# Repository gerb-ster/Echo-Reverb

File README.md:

# Echo/Reverb

Next, another effect module. I bought a bunch of PT2399 IC’s from China so I made his Echo/Reverb unit. It’s basically a clone of the Echo unit from Synthrotek.

## Status: Finished

- done: first schematic & board design
- done: breadboard and test
- done: design frontpanel
- done: order PCB and build prototype

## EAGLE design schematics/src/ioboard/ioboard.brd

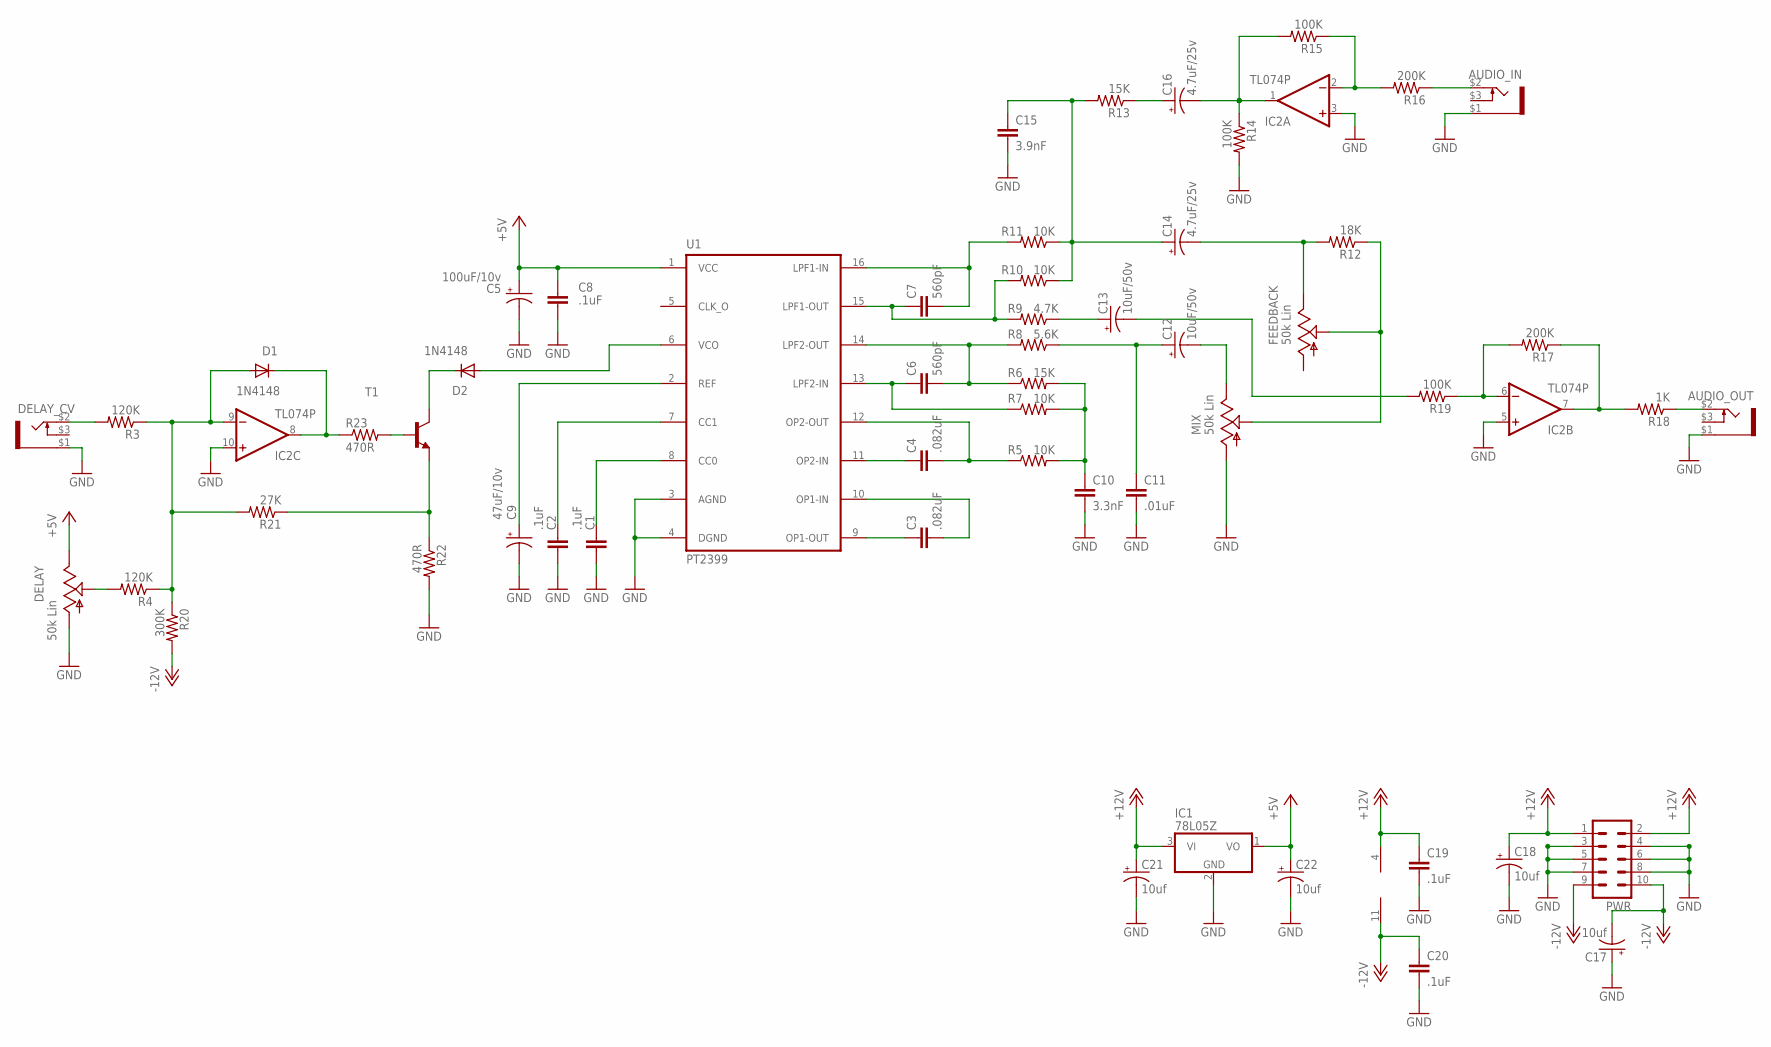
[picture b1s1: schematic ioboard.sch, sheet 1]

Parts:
AUDIO_IN: PJ-323PJ-323; PJ-323
AUDIO_OUT: PJ-323PJ-323; PJ-323
C1, C2, C8, C19, C20: .1uF; C050-024X044
C3, C4: .082uF; C050-024X044
C5: 100uF/10v; E2,5-6
C6, C7: 560pF; C050-024X044
C9: 47uF/10v; E2,5-6
C10: 3.3nF; C050-024X044
C11: .01uF; C050-024X044
C12, C13: 10uF/50v; E2,5-6
C14, C16: 4.7uF/25v; E2,5-6
C15: 3.9nF; C050-024X044
C17, C18, C21, C22: 10uf; E2,5-5
D1, D2: 1N4148; DO35-7
DELAY: 50k Lin; EVUF
DELAY_CV: PJ-323PJ-323; PJ-323
FEEDBACK: 50k Lin; EVUF
IC1: 78L05Z; TO92
IC2: TL074P; DIL14
MIX: 50k Lin; EVUF
PWR: ML10
R3, R4: 120K; 0207/7
R5, R7, R10, R11: 10K; 0207/7
R6, R13: 15K; 0207/7
R8: 5.6K; 0207/7
R9: 4.7K; 0207/7
R12: 18K; 0207/7
R14, R15, R19: 100K; 0207/7
R16, R17: 200K; 0207/7
R18: 1K; 0207/7
R20: 300K; 0207/7
R21: 27K; 0207/7
R22, R23: 470R; 0207/7
T1: 2N3904-NPN-TO92-EBC; TO92-EBC
U1: PT2399; DIL16

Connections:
+5V: C5.+, C8.1, C22.+, DELAY.3 (E), IC1.1 (VO), U1.1 (VCC)
+12V: C18.+, C19.1, C21.+, IC1.3 (VI), IC2.4 (V+), PWR.1, PWR.2
-12V: C17.-, C20.1, IC2.11 (V-), PWR.9, PWR.10, R20.2
DELAY: D2.A, U1.6 (VCO)
GND: AUDIO_IN.$1 (3), AUDIO_OUT.$1 (3), C1.2, C2.2, C5.-, C8.2, C9.-, C10.2, C11.2, C15.2, C17.+, C18.-, C19.2, C20.2, C21.-, C22.-, DELAY.1 (A), DELAY_CV.$1 (3), IC1.2 (GND), IC2.3 (+IN), IC2.5 (+IN), IC2.10 (+IN), MIX.1 (A), PWR.3, PWR.4, PWR.5, PWR.6, PWR.7, PWR.8, R14.2, R22.2, U1.3 (AGND), U1.4 (DGND)
unnamed: C1.1, U1.8 (CC0)
unnamed: C2.1, U1.7 (CC1)
unnamed: C3.2, U1.10 (OP1-IN)
unnamed: C3.1, U1.9 (OP1-OUT)
unnamed: C4.1, U1.11 (OP2-IN)
unnamed: C4.2, R5.1, U1.12 (OP2-OUT)
unnamed: C6.1, R7.1, U1.13 (LPF2-IN)
unnamed: C7.1, R9.2, R10.2, U1.15 (LPF1-OUT)
unnamed: C6.2, R6.1, R8.2, U1.14 (LPF2-OUT)
unnamed: C7.2, R11.2, U1.16 (LPF1-IN)
unnamed: C9.+, U1.2 (REF)
unnamed: C10.1, R5.2, R6.2, R7.2
unnamed: C11.1, C12.+, R8.1
unnamed: C12.-, MIX.3 (E)
unnamed: C13.+, R9.1
unnamed: C14.+, C15.1, R10.1, R11.1, R13.2
unnamed: C14.-, FEEDBACK.3 (E), R12.2
unnamed: FEEDBACK.2 (S), MIX.2 (S), R12.1
unnamed: C16.+, R13.1
unnamed: C16.-, IC2.1 (OUT), R14.1, R15.2
unnamed: IC2.6 (-IN), R17.2, R19.1
unnamed: AUDIO_IN.$2 (1), R16.1
unnamed: IC2.2 (-IN), R15.1, R16.2
unnamed: IC2.7 (OUT), R17.1, R18.2
unnamed: AUDIO_OUT.$2 (1), R18.1
unnamed: DELAY.2 (S), R4.2
unnamed: DELAY_CV.$2 (1), R3.2
unnamed: D1.A, IC2.9 (-IN), R3.1, R4.1, R20.1, R21.2
unnamed: D1.C, IC2.8 (OUT), R23.1
unnamed: R21.1, R22.1, T1.E
unnamed: R23.2, T1.B
unnamed: D2.C, T1.C
OUT: C13.-, R19.2

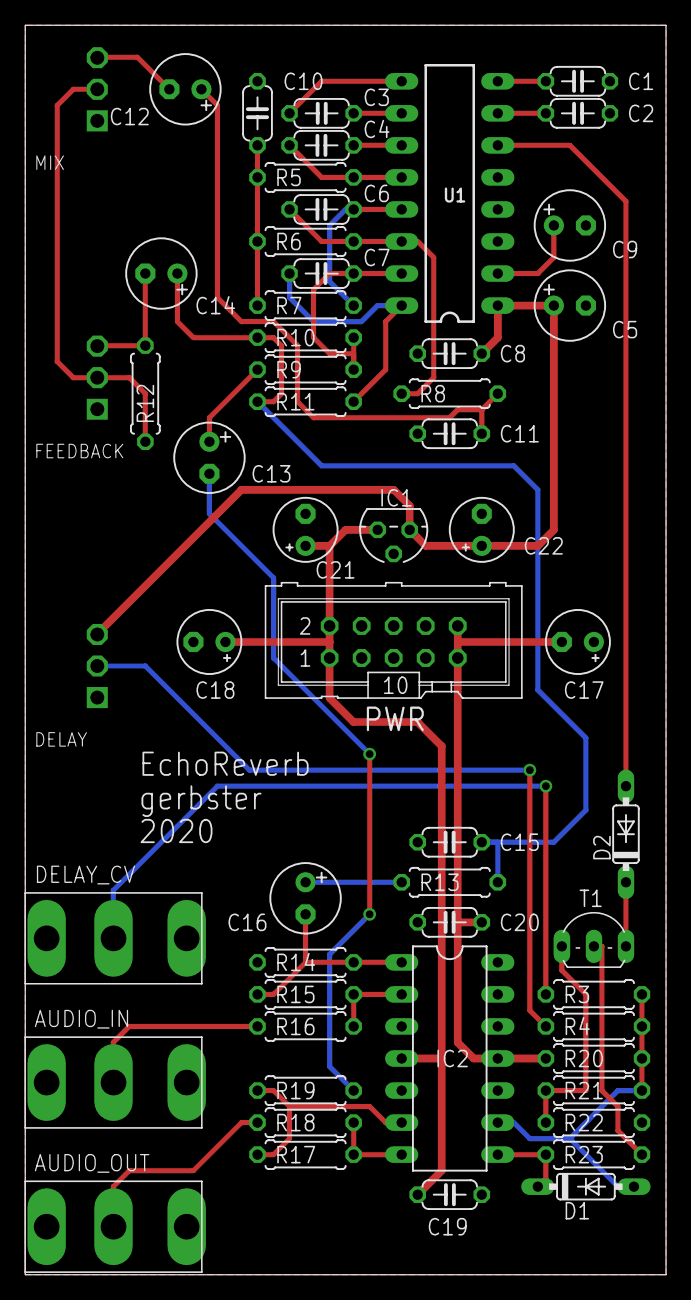
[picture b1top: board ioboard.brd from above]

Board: 2 copper layers, 50.8 x 99.1 mm, 56 parts (0 on the bottom side), 38 nets.

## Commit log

2021-05-06 some files
2021-05-07 Added files & structure
2021-05-10 Added Status
2021-05-11 Added Status & Images
2021-08-06 Updated some schematics and docs
2021-08-10 Fixed some bugs and updated documentation
2022-04-20 Some updates & bugfixes
2022-04-22 Fixed schematics & descriptions
2022-05-17 Updated Firmware
2022-05-18 Updated Faceplates
2022-05-18 Fixed issues
2022-05-21 Fixed schematics
2022-05-28 General updates
